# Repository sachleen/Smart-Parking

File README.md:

Smart Parking ([GitHub][1])
=============

A system to monitor parking space availability and help drivers quickly find a nearby place to park.

[California State University, Sacramento][2]

Computer Engineering Senior Design Project

Team #4

 - Sachleen Sandhu
 - Caleb Fountain
 - Phillip Booker

  [1]: https://github.com/sachleen/Smart-Parking
  [2]: http://csus.edu

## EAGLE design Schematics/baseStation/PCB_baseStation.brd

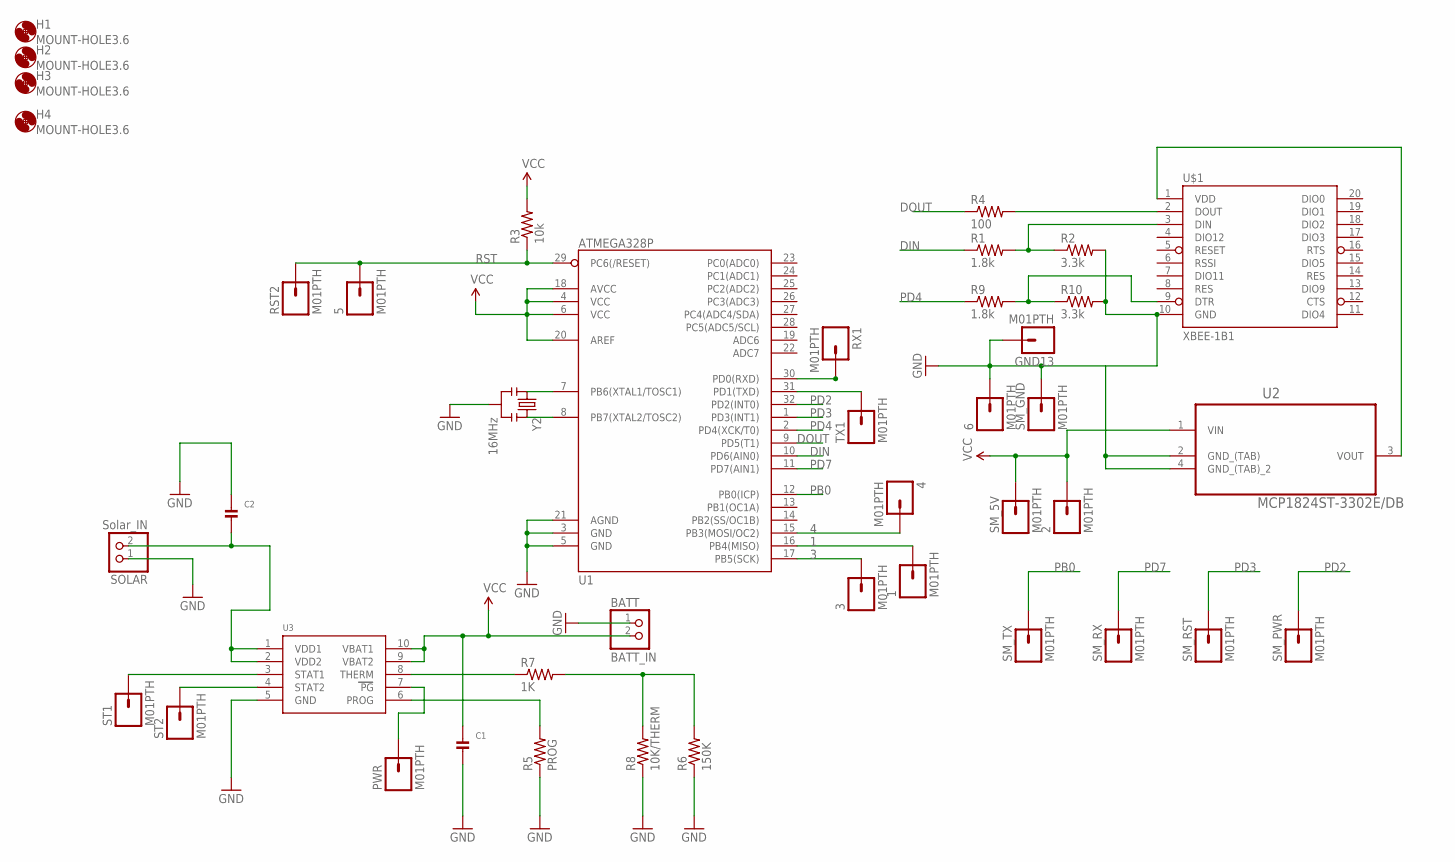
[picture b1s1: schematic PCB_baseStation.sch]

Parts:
1, 2, 3, 4, 5, 6: M01PTH; 1X01
BATT: BATT_IN; JSTPH2
C1, C2: CAP_CERAMIC0805; 0805
GND13: M01PTH; 1X01
H1, H2, H3, H4: MOUNT-HOLE3.6; 3,6
PWR: M01PTH; 1X01
R1, R9: 1.8k; 0603-RES
R2, R10: 3.3k; 0603-RES
R3: 10k; 1206
R4: 100; 0603-RES
R5: PROG; 0805-THM
R6: 150K; M0805
R7: 1K; M0805
R8: 10K/THERM; 0805-THM
RST2: M01PTH; 1X01
RX1: M01PTH; 1X01
SM_5V: M01PTH; 1X01
SM_GND: M01PTH; 1X01
SM_PWR: M01PTH; 1X01
SM_RST: M01PTH; 1X01
SM_RX: M01PTH; 1X01
SM_TX: M01PTH; 1X01
SOLAR: Solar_IN; JSTPH2
ST1, ST2: M01PTH; 1X01
TX1: M01PTH; 1X01
U1: ATMEGA328P; TQFP32-08
U2: MCP1824ST-3302E/DB; SOT230P700X180-4N
U3: MCP73833; MSOP10
U$1: XBEE-1B1; XBEE-1
Y2: 16MHz; RESONATOR-SMD

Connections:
1: 1.1, U1.16 (PB4(MISO))
3: 3.1, U1.17 (PB5(SCK))
4: 4.1, U1.15 (PB3(MOSI/OC2))
DIN: R1.1, U1.10 (PD6(AIN0))
DOUT: R4.1, U1.9 (PD5(T1))
GND: 6.1, BATT.1, C1.2, C2.1, GND13.1, R2.2, R5.1, R6.1, R8.1, R10.2, SM_GND.1, SOLAR.1, U1.3 (GND), U1.5 (GND), U1.21 (AGND), U2.2 (GND_(TAB)), U2.4 (GND_(TAB)_2), U3.5 (GND), U$1.10 (GND), Y2.2
unnamed: ST1.1, U3.3 (STAT1)
unnamed: ST2.1, U3.4 (STAT2)
unnamed: R1.2, R2.1, U$1.3 (DIN)
unnamed: R4.2, U$1.2 (DOUT)
unnamed: R9.2, R10.1, U$1.9 (DTR)
unnamed: U1.7 (PB6(XTAL1/TOSC1)), Y2.1
unnamed: U1.8 (PB7(XTAL2/TOSC2)), Y2.3
unnamed: C2.2, SOLAR.2, U3.1 (VDD1), U3.2 (VDD2)
unnamed: R5.2, U3.6 (PROG)
unnamed: PWR.1, U3.7 (PG)
unnamed: R6.2, R7.2, R8.2
unnamed: U2.3 (VOUT), U$1.1 (VDD)
unnamed: R7.1, U3.8 (THERM)
unnamed: TX1.1, U1.31 (PD1(TXD))
unnamed: RX1.1, U1.30 (PD0(RXD))
PB0: SM_TX.1, U1.12 (PB0(ICP))
PD2: SM_PWR.1, U1.32 (PD2(INT0))
PD3: SM_RST.1, U1.1 (PD3(INT1))
PD4: R9.1, U1.2 (PD4(XCK/T0))
PD7: SM_RX.1, U1.11 (PD7(AIN1))
RST: 5.1, R3.1, RST2.1, U1.29 (PC6(/RESET))
VCC: 2.1, BATT.2, C1.1, R3.2, SM_5V.1, U1.4 (VCC), U1.6 (VCC), U1.18 (AVCC), U1.20 (AREF), U2.1 (VIN), U3.9 (VBAT2), U3.10 (VBAT1)

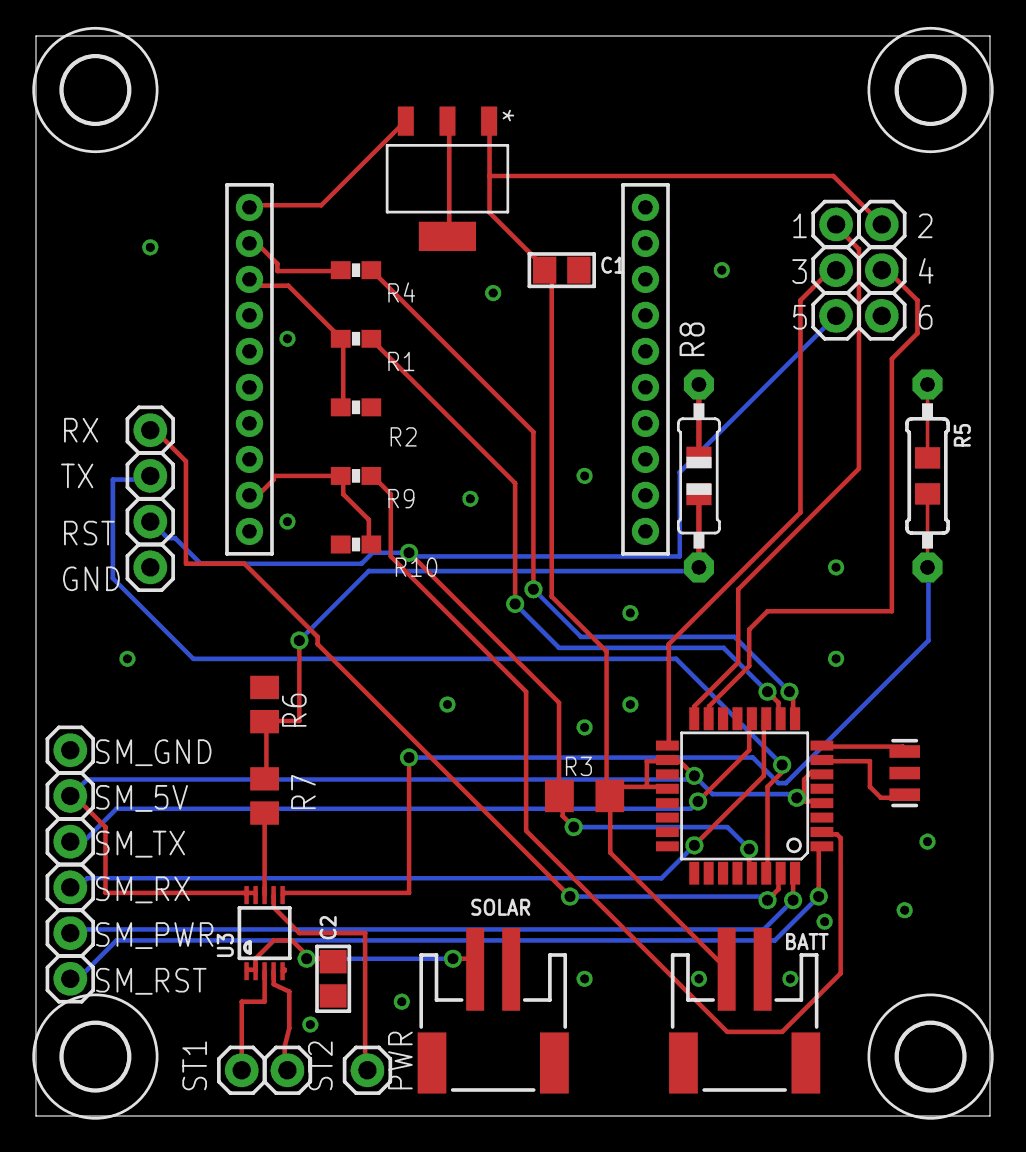
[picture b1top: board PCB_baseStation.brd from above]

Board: 2 copper layers, 53.0 x 60.0 mm, 42 parts (0 on the bottom side), 28 nets.

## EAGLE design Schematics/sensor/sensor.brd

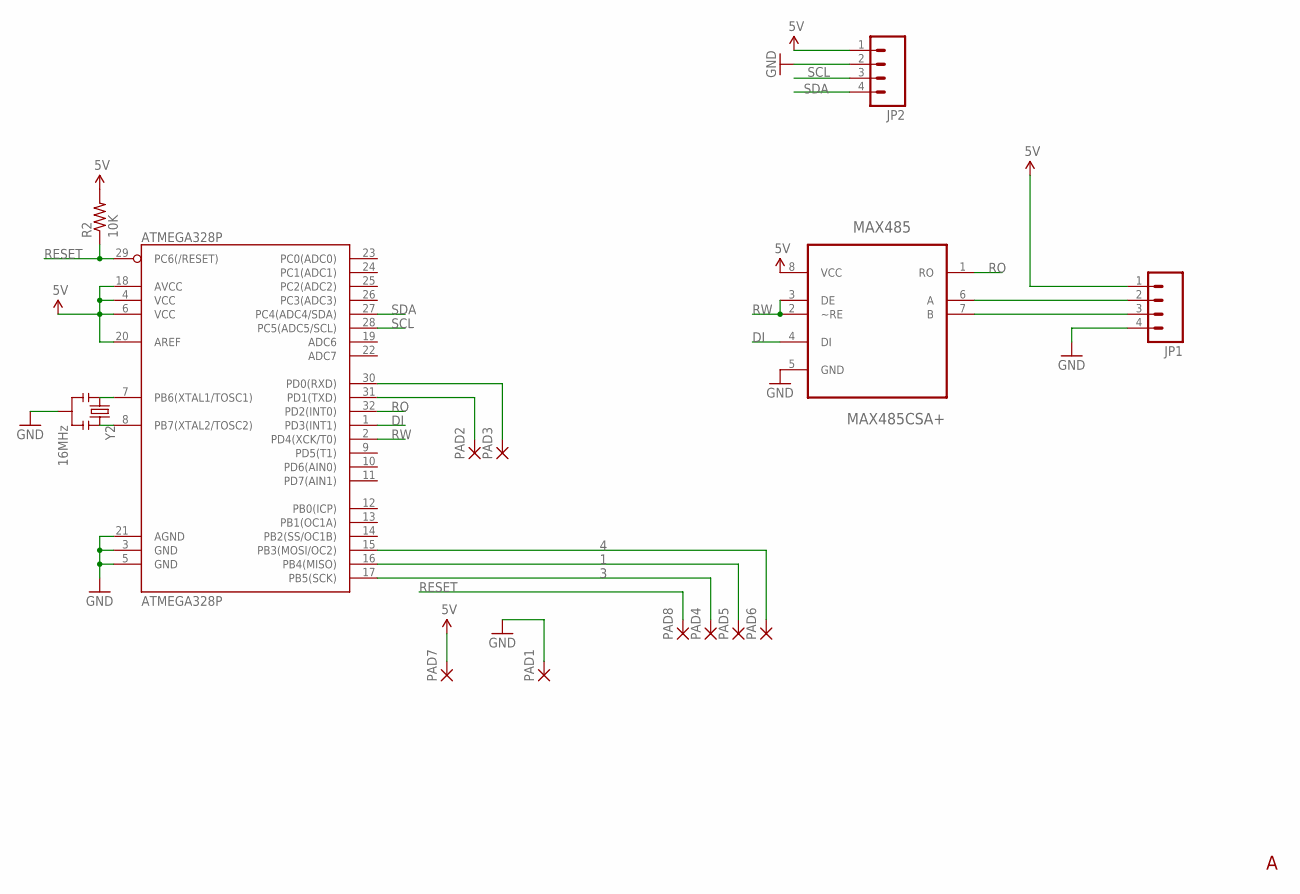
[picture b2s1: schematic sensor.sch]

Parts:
ATMEGA328P: ATMEGA328P; TQFP32-08
JP1, JP2: M04PTH; 1X04
MAX485: MAX485CSA+; SOIC127P600X175-8N
PAD1, PAD2, PAD3, PAD4, PAD5, PAD6, PAD7, PAD8: 1,6/0,9
R2: 10K; 0603-RES
Y2: 16MHz; RESONATOR-SMD

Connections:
1: ATMEGA328P.16 (PB4(MISO)), PAD5.1
3: ATMEGA328P.17 (PB5(SCK)), PAD4.1
4: ATMEGA328P.15 (PB3(MOSI/OC2)), PAD6.1
5V: ATMEGA328P.4 (VCC), ATMEGA328P.6 (VCC), ATMEGA328P.18 (AVCC), ATMEGA328P.20 (AREF), JP1.1, JP2.1, MAX485.8 (VCC), PAD7.1, R2.2
DI: ATMEGA328P.1 (PD3(INT1)), MAX485.4 (DI)
GND: ATMEGA328P.3 (GND), ATMEGA328P.5 (GND), ATMEGA328P.21 (AGND), JP1.4, JP2.2, MAX485.5 (GND), PAD1.1, Y2.2
unnamed: ATMEGA328P.7 (PB6(XTAL1/TOSC1)), Y2.1
unnamed: ATMEGA328P.8 (PB7(XTAL2/TOSC2)), Y2.3
unnamed: ATMEGA328P.30 (PD0(RXD)), PAD3.1
unnamed: JP1.2, MAX485.6 (A)
unnamed: JP1.3, MAX485.7 (B)
unnamed: ATMEGA328P.31 (PD1(TXD)), PAD2.1
RESET: ATMEGA328P.29 (PC6(/RESET)), PAD8.1, R2.1
RO: ATMEGA328P.32 (PD2(INT0)), MAX485.1 (RO)
RW: ATMEGA328P.2 (PD4(XCK/T0)), MAX485.2 (~RE), MAX485.3 (DE)
SCL: ATMEGA328P.28 (PC5(ADC5/SCL)), JP2.3
SDA: ATMEGA328P.27 (PC4(ADC4/SDA)), JP2.4

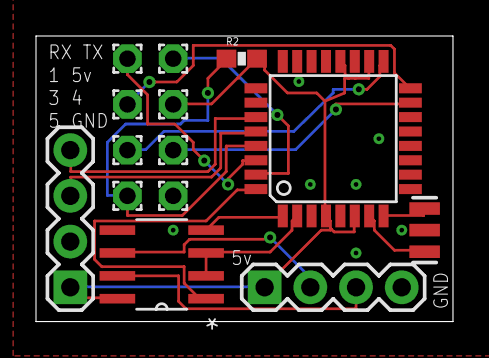
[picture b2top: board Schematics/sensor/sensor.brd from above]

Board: 2 copper layers, 23.2 x 15.9 mm, 14 parts (0 on the bottom side), 17 nets.

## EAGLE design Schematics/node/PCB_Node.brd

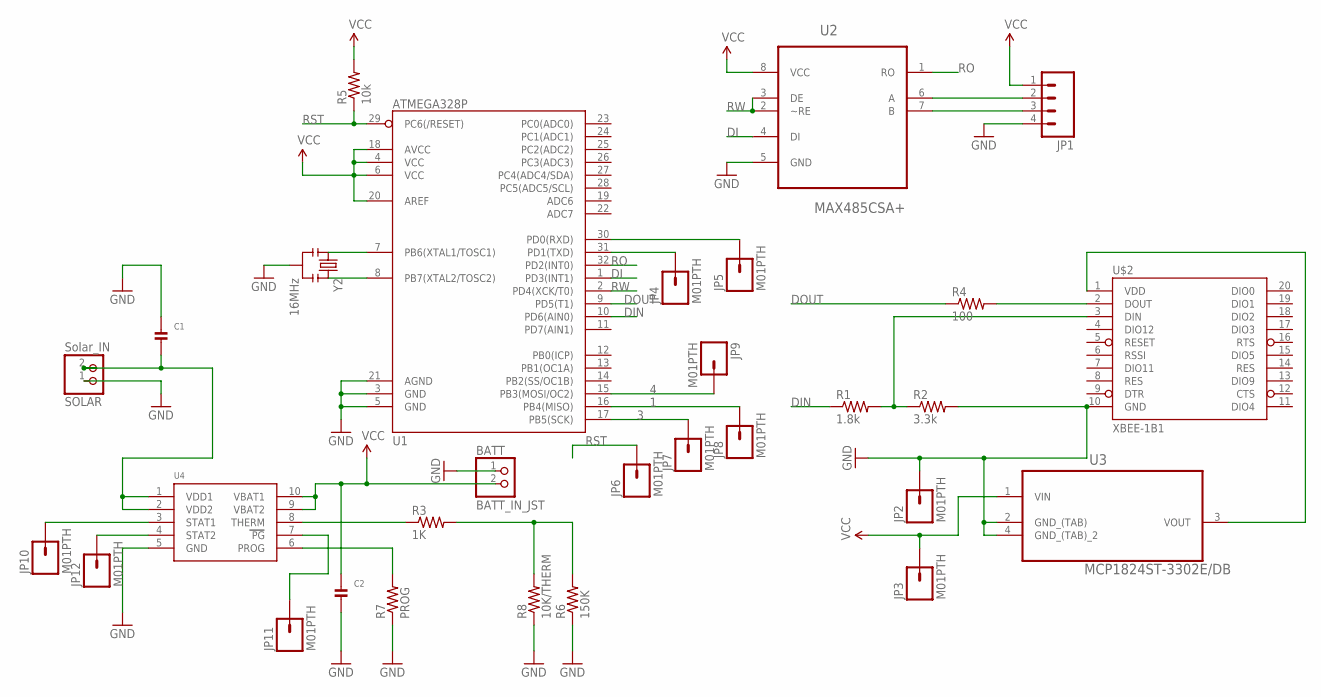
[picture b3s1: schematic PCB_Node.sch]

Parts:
BATT: BATT_IN_JST; JSTPH2
C1, C2: CAP_CERAMIC0805; 0805
JP1: M04PTH; 1X04
JP2, JP3, JP4, JP5, JP6, JP7, JP8, JP9, JP10, JP11, JP12: M01PTH; 1X01
R1: 1.8k; 0603-RES
R2: 3.3k; 0603-RES
R3: 1K; R0805
R4: 100; 0603-RES
R5: 10k; 0603-RES
R6: 150K; R0805
R7: PROG; 0805-THM
R8: 10K/THERM; 0805-THM
SOLAR: Solar_IN; JSTPH2
U1: ATMEGA328P; TQFP32-08
U2: MAX485CSA+; SOIC127P600X175-8N
U3: MCP1824ST-3302E/DB; SOT230P700X180-4N
U4: MCP73833; MSOP10
U$2: XBEE-1B1; XBEE-1
Y2: 16MHz; RESONATOR-SMD

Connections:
1: JP8.1, U1.16 (PB4(MISO))
3: JP7.1, U1.17 (PB5(SCK))
4: JP9.1, U1.15 (PB3(MOSI/OC2))
DI: U1.1 (PD3(INT1)), U2.4 (DI)
DIN: R1.1, U1.10 (PD6(AIN0))
DOUT: R4.1, U1.9 (PD5(T1))
GND: BATT.1, C1.1, C2.2, JP1.4, JP2.1, R2.2, R6.1, R7.1, R8.1, SOLAR.1, U1.3 (GND), U1.5 (GND), U1.21 (AGND), U2.5 (GND), U3.2 (GND_(TAB)), U3.4 (GND_(TAB)_2), U4.5 (GND), U$2.10 (GND), Y2.2
unnamed: R4.2, U$2.2 (DOUT)
unnamed: R1.2, R2.1, U$2.3 (DIN)
unnamed: R7.2, U4.6 (PROG)
unnamed: U3.3 (VOUT), U$2.1 (VDD)
unnamed: R3.1, U4.8 (THERM)
unnamed: R3.2, R6.2, R8.2
unnamed: C1.2, SOLAR.2, U4.1 (VDD1), U4.2 (VDD2)
unnamed: JP10.1, U4.3 (STAT1)
unnamed: JP12.1, U4.4 (STAT2)
unnamed: JP11.1, U4.7 (PG)
unnamed: U1.8 (PB7(XTAL2/TOSC2)), Y2.3
unnamed: U1.7 (PB6(XTAL1/TOSC1)), Y2.1
unnamed: JP4.1, U1.31 (PD1(TXD))
unnamed: JP5.1, U1.30 (PD0(RXD))
unnamed: JP1.2, U2.6 (A)
unnamed: JP1.3, U2.7 (B)
RO: U1.32 (PD2(INT0)), U2.1 (RO)
RST: JP6.1, R5.1, U1.29 (PC6(/RESET))
RW: U1.2 (PD4(XCK/T0)), U2.2 (~RE), U2.3 (DE)
VCC: BATT.2, C2.1, JP1.1, JP3.1, R5.2, U1.4 (VCC), U1.6 (VCC), U1.18 (AVCC), U1.20 (AREF), U2.8 (VCC), U3.1 (VIN), U4.9 (VBAT2), U4.10 (VBAT1)

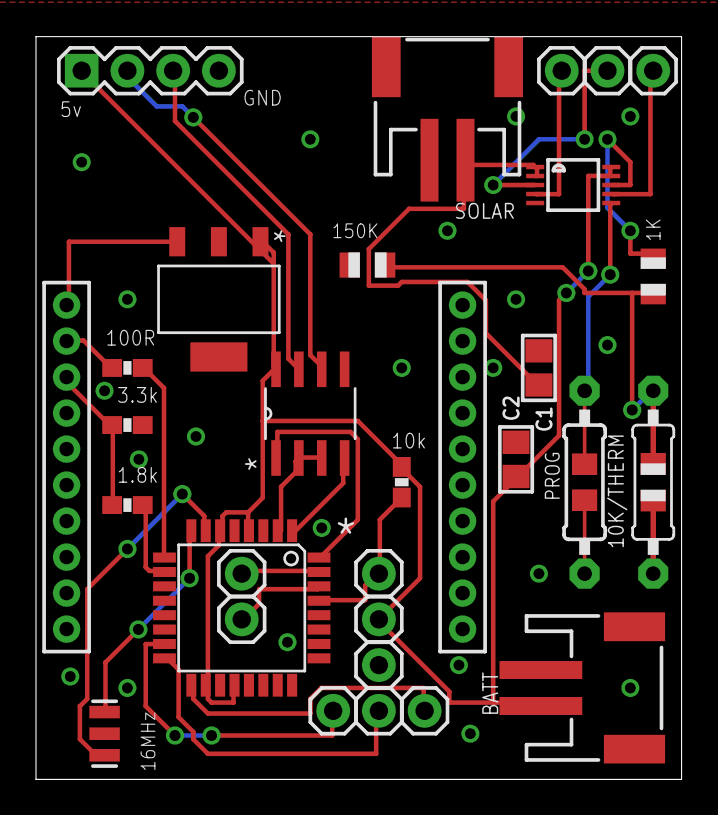
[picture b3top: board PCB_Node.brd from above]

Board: 2 copper layers, 35.9 x 41.3 mm, 30 parts (0 on the bottom side), 27 nets.

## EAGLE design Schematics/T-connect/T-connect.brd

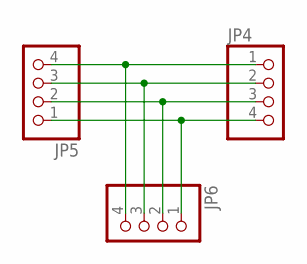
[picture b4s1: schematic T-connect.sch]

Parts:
JP4, JP5, JP6: PINHD-1X4/90; 1X04/90

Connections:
unnamed: JP4.1, JP5.4, JP6.4
unnamed: JP4.2, JP5.3, JP6.3
unnamed: JP4.3, JP5.2, JP6.2
unnamed: JP4.4, JP5.1, JP6.1

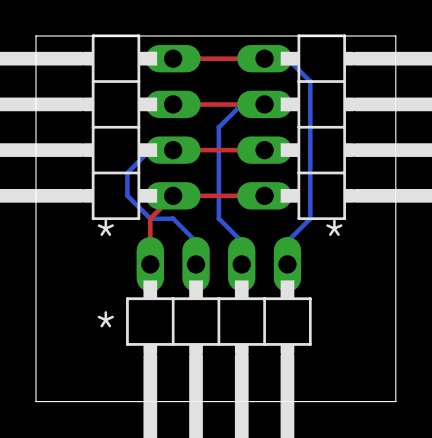
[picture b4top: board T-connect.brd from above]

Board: 2 copper layers, 20.0 x 20.3 mm, 3 parts (0 on the bottom side), 4 nets.

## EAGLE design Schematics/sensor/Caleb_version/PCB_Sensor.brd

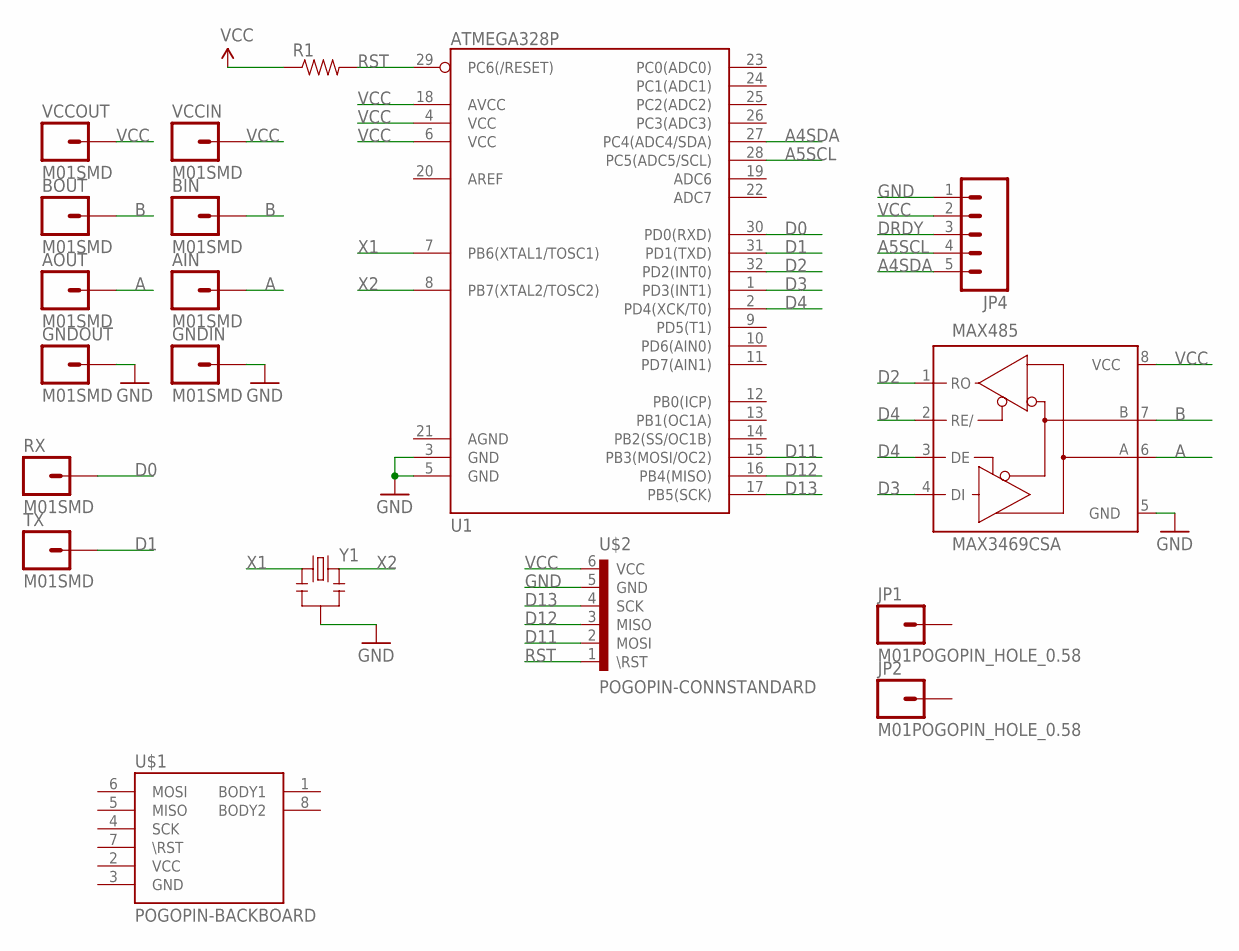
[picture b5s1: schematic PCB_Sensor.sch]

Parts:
AIN: M01SMD; LUXEON-PAD
AOUT: M01SMD; LUXEON-PAD
BIN: M01SMD; LUXEON-PAD
BOUT: M01SMD; LUXEON-PAD
GNDIN: M01SMD; LUXEON-PAD
GNDOUT: M01SMD; LUXEON-PAD
JP1, JP2: M01POGOPIN_HOLE_0.58; 1X01_POGOPIN_HOLE_0.58
JP4: M05PTH; 1X05
MAX485: MAX3469CSA; SO08
R1: RESISTOR1206; 1206
RX: M01SMD; LUXEON-PAD
TX: M01SMD; LUXEON-PAD
U1: ATMEGA328P; TQFP32-08
U$1: POGOPIN-BACKBOARD; POGOPROG-BACKMOUNT
U$2: POGOPIN-CONNSTANDARD; POGOPROG-CONN
VCCIN: M01SMD; LUXEON-PAD
VCCOUT: M01SMD; LUXEON-PAD
Y1: RESONATORPTH; RESONATOR-PTH

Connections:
A: AIN.P$1, MAX485.6 (A)
A4SDA: JP4.5, U1.27 (PC4(ADC4/SDA))
A5SCL: JP4.4, U1.28 (PC5(ADC5/SCL))
B: BIN.P$1, MAX485.7 (B)
D0: U1.30 (PD0(RXD))
D1: U1.31 (PD1(TXD))
D2: MAX485.1 (RO), U1.32 (PD2(INT0))
D3: MAX485.4 (DI), U1.1 (PD3(INT1))
D4: MAX485.2 (RE/), MAX485.3 (DE), U1.2 (PD4(XCK/T0))
D11: U1.15 (PB3(MOSI/OC2)), U$2.2 (MOSI)
D12: U1.16 (PB4(MISO)), U$2.3 (MISO)
D13: U1.17 (PB5(SCK)), U$2.4 (SCK)
DRDY: JP4.3
GND: GNDIN.P$1, JP4.1, MAX485.5 (GND), U1.3 (GND), U1.5 (GND), U$2.5 (GND), Y1.2
RST: R1.2, U1.29 (PC6(/RESET)), U$2.1 (\RST)
VCC: JP4.2, MAX485.8 (VCC), R1.1, U1.4 (VCC), U1.6 (VCC), U1.18 (AVCC), U$2.6 (VCC), VCCIN.P$1, VCCOUT.P$1
X1: U1.7 (PB6(XTAL1/TOSC1)), Y1.1
X2: U1.8 (PB7(XTAL2/TOSC2)), Y1.3

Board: 2 copper layers, 19 parts (0 on the bottom side), 15 nets, no tracks yet.

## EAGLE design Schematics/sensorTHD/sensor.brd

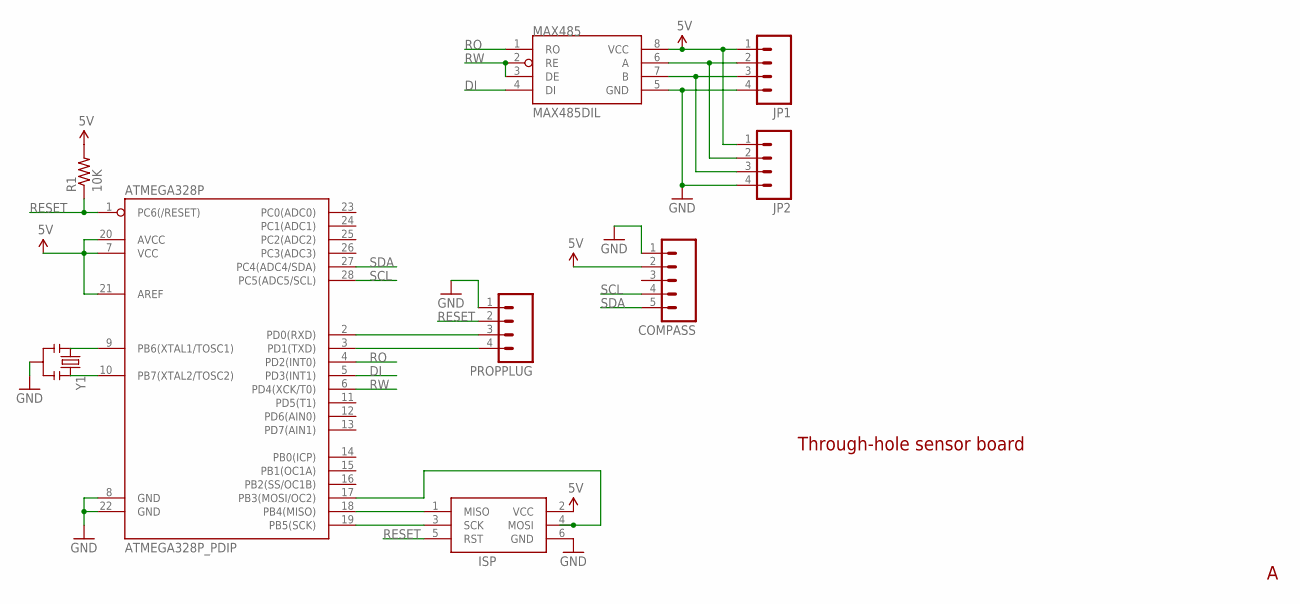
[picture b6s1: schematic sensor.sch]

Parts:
ATMEGA328P: ATMEGA328P_PDIP; DIL28-3
COMPASS: M05PTH; 1X05
ISP: AVRISP-6; AVRISP
JP1, JP2: M04PTH; 1X04
MAX485: MAX485DIL; DIL08
PROPPLUG: M04PTH; 1X04
R1: 10K; AXIAL-0.4
Y1: RESONATORPTH; RESONATOR-PTH

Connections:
5V: ATMEGA328P.7 (VCC), ATMEGA328P.20 (AVCC), ATMEGA328P.21 (AREF), COMPASS.2, ISP.2 (VCC), JP1.1, JP2.1, MAX485.8 (VCC), R1.P$2 (2)
DI: ATMEGA328P.5 (PD3(INT1)), MAX485.4 (DI)
GND: ATMEGA328P.8 (GND), ATMEGA328P.22 (GND), COMPASS.1, ISP.6 (GND), JP1.4, JP2.4, MAX485.5 (GND), PROPPLUG.1, Y1.2
unnamed: ATMEGA328P.10 (PB7(XTAL2/TOSC2)), Y1.3
unnamed: ATMEGA328P.9 (PB6(XTAL1/TOSC1)), Y1.1
unnamed: ATMEGA328P.18 (PB4(MISO)), ISP.1 (MISO)
unnamed: ATMEGA328P.19 (PB5(SCK)), ISP.3 (SCK)
unnamed: ATMEGA328P.17 (PB3(MOSI/OC2)), ISP.4 (MOSI)
unnamed: ATMEGA328P.2 (PD0(RXD)), PROPPLUG.3
unnamed: ATMEGA328P.3 (PD1(TXD)), PROPPLUG.4
unnamed: JP1.3, JP2.3, MAX485.7 (B)
unnamed: JP1.2, JP2.2, MAX485.6 (A)
RESET: ATMEGA328P.1 (PC6(/RESET)), ISP.5 (RST), PROPPLUG.2, R1.P$1 (1)
RO: ATMEGA328P.4 (PD2(INT0)), MAX485.1 (RO)
RW: ATMEGA328P.6 (PD4(XCK/T0)), MAX485.2 (RE), MAX485.3 (DE)
SCL: ATMEGA328P.28 (PC5(ADC5/SCL)), COMPASS.4
SDA: ATMEGA328P.27 (PC4(ADC4/SDA)), COMPASS.5

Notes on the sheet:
Through-hole sensor board

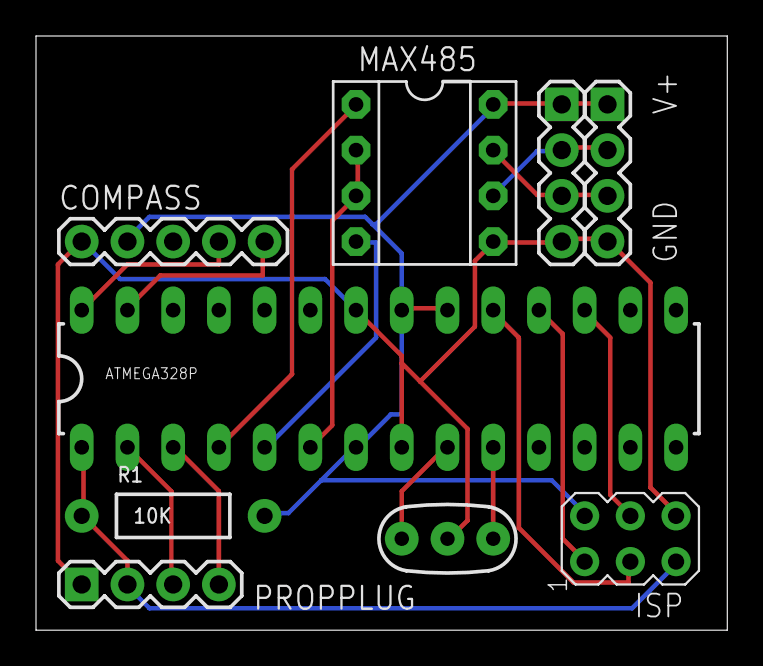
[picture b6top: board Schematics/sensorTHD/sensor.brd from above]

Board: 2 copper layers, 38.4 x 33.0 mm, 9 parts (0 on the bottom side), 17 nets.

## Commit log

2014-01-02 no message
2014-01-02 test
2014-01-02 Creating folder structure
2014-01-02 Added team info
2014-01-03 Initial commit.
2014-01-05 Worked on adding and editing Node markers on map. Still need to add delete feature.
2014-01-05 Added delete function Cleaned up (removed) console.log messages
2014-01-05 Front end functionality complete. Add/Delete nodes works.
2014-01-06 Added database functionality. Create, Edit, Delete work.
2014-01-06 App parses responses from server and displays user-friendly message now.
2014-01-06 Fancy message boxes!
2014-01-06 Created simple client app
2014-01-06 Opens device's Maps app when clicking on marker
2014-01-06 Clean up.
2014-01-07 Client updates automatically as map is panned. Loads all markers within a fixed distance of the map center.
2014-01-07 Added current location marker
2014-01-07 Added production/development modes
2014-01-07 Handled case where zooming in/out was not triggering new data load
2014-01-07 Made dev/prod mode switching easier.
2014-01-07 Put distance calculating SQL query into a function. Removed mysql passwords from index.php. oops
2014-01-07 Added htaccess to deny access to vendor directory
2014-01-10 Added a license
2014-02-02 Sensor schematics and board layouts
2014-02-02 Changed headers for 485 bus and added more labels.
2014-02-08 Made sensor PCB smaller. Removed through hole circuit.
2014-02-09 Admin app only loads nodes within 1mi radius of map center now.
2014-02-09 Top/bottom ground planes weren't connected. Added via to connect them.
2014-02-11 Testing commit to README.md
2014-02-11 Revert "Testing commit to README.md"
    This reverts commit b2356239c0976946008ed139fd2cdaf01c163b69.
2014-02-14 Added simple API key authentication to update/delete methods.
2014-02-14 changed = to == in if statement.
2014-02-14 Updated db schema to for new api keys table
2014-02-17 RX and TX for PROPPLUG weren't connected. they are now.
2014-02-21 added config files for client/server apps
2014-02-22 * Updated api key privileges - combined create_or_update with delete. * convert node ID to upper case before storing it in database.
2014-02-22 Added history logging functionality.
2014-02-22 BASE_URL should contain trailing slash.
2014-02-22 Fixed typo
2014-02-23 Removed unused keys from response.
2014-02-23 Code cleanup
2014-02-24 Added ignore entry for eagle project file.
2014-03-01 Added function to get node info.
2014-03-02 Connector changed
    I changed connectors to the following
    Device: M01SMD (M01)
    Package: LUXEON-PAD
    Library: SparkFun-Connectors
2014-03-02 Revision by Caleb
    Changed programming connectors to be on the surface as pads only for
    programming with another board.
    Rearranged the board to minimize the size as much as possible.
    Dimensions are .95 x .65
2014-03-02 PCB Node
    Created schematic and board layout for Node PCB
2014-03-02 New test script. Initial commit.
2014-03-02 better eagle ignore rules.
2014-03-03 added more test cases
2014-03-15 Added my current code for Base and Node
2014-03-15 Initial commit for analytics site
2014-03-15 re-added /nodes/all function
2014-03-17 Added auto run script for demo of client app
2014-03-17 Shortened refresh timeout to 2 seconds (from 10s) and added auto refresh functionality.
2014-03-17 renamed centerChanged function to more generic loadNodesAtCurrentPosition
2014-03-17 Set timeout to 5s. Map only updates markers when there's a change. Added bounce animation on change.
2014-03-17 changed refresh rate.
2014-03-17 cleaned up marker animation code
2014-03-17 cleaned up code
2014-03-17 marker indicator count updates after animation to make it easier to see the change.
2014-03-17 added nodes list for some nodes on the production site.
2014-03-20 Cleaned up sensor code, split up main code from RS485 code. Added debug functions instead of Searial.println
2014-03-20 Updated Base and Node codes
2014-03-21 Converted wired communication stuff to a class.
2014-03-21 fixed typo in debug_init function.
2014-03-21 Changed all Serial prints to DEBUG. Integrated with WiredCommunication class.
2014-03-21 PCB updates
    changed sensor PCB to 3.0
    changed Node PCB to 2.0 and parts list to go with it (Sach, can you
    look over the schematic, board, and parts list that I have so far to
    make sure I have everything correct?)
    added Base Station PCB 0.5
2014-03-21 Corrected Node PCB issues found by Sachleen for version 2.0
2014-03-22 Added XBee communication class. Not integrated with Node code, yet.
2014-03-22 Moved RS485 initialization into WiredCommunication class.
2014-03-22 Remove old files
2014-03-22 Renamed new files.
2014-03-22 Include globals in WiredCommunications to allow for debug prints
2014-03-22 send message accepts an id and a message.
2014-03-23 changed message packet format to include sender and receiver.
2014-03-23 Using new communication functions.
2014-03-23 Accidentally uploaded Node as a C header file...
2014-03-23 add debug prints in xbee class. add xbee class to base
2014-03-23 have to include softwareserial in xbee comm... added globals.
2014-03-23 off by 1 error in message format
2014-03-23 Fixed ACK bug where sendMessage was always returning false because of \r\n at end of message.
2014-03-23 Trimmed response Strings
2014-03-23 Fixed Node Parsing
2014-03-23 Removed ACK checks
2014-03-23 Taking out acknowledges
2014-03-23 removed acknowledge stuff...
2014-03-23 Node Fixes
    Made fixes to Node PCB.
    - connected solar power to charging chip
    - made power to battery and atmega from charging chip only
    - rearranged board for these changes to work
2014-03-24 Completed SIM900 Communication class. Have methods to send commands and make HTTP Requests. Includes demo application.
2014-03-24 spacing
2014-03-25 Node fixes
    Corrected the c1 capacitor connected to solar power correctly
    moved part names to locations where they will be read because of vias
    blocking them
2014-03-25 Changed API keys in test scripts.
2014-03-29 Added SIM and Sleep functions
2014-03-29 fixed POST url
2014-03-29 Cleaned out unneeded functions
2014-03-29 Chenged api key
2014-03-29 removed call to freeram function
2014-03-29 Fixed bug where xbee and simcomm wouldn't work together. needed to switch between software serial devices.
2014-03-29 save ram store strings in flash
2014-03-29 Checked for NULL response from sim function
2014-03-29 trying to free memory
2014-03-30 Trying to cut Base code
2014-03-30 added free ram code
2014-03-30 Cut out N case
2014-03-30 Commented out debug messages
2014-03-30 minimal code for U command only. THIS WORKS.
2014-03-30 Hard coded URLs.
2014-03-30 Reverted to old code to test (left working one in comments)
2014-03-30 removed GET request functionality
2014-03-30 proper call to POST method
2014-03-30 Reverting to what worked after failed attempts...
2014-03-30 All code works with POST method only.
2014-03-31 PCB improvements
    Node_SP 2.0: moved some text to the back layer
    Sen_SP 4.0: improved the board for programming and changed the
    resonator from through hole to surface mount - then rearranged the
    items on the board to make it smaller
2014-03-31 Power optimizations in sensor.
2014-04-02 moved DEBUG_ENABLE line from globals.h to individual files
2014-04-02 Toggles power when it needs to send updates to the server
2014-04-02 compass sleep mode. saves about 0.1mA
2014-04-04 Base Station PCB 1.0
    Finished Base Station PCB design version 1.0
2014-04-06 Added Xbee and arduino sleep to Node
2014-04-06 Took out sleep library
2014-04-06 Base Station PCB improvements
    Base_SP 1.1
    moved prop plug and ISP closer in
    added two resistors to limit voltage from arduino to xbee pin 9(SLP)
2014-04-06 Base Station PCB Improvements
    Base_SP 1.2
    moved components around to group them better
    corrected xbee pin 9 to be connected from arduino PD4 to PD7
2014-04-07 Base Station PCB Improvements
    Base_SP 1.3
    fixed SIM900 pins that go to Arduino
    changed xbee pin that goes to Arduino
    created table of base Arduino pins and where they go to
2014-04-07 Revert 84d25af..6e9f095
    This rolls back to commit 84d25afdcd8c89c582355f2af172ebeae3c02958.
2014-04-07 Revert f17e3e6..3ebf404
    This rolls back to commit f17e3e6aa3351730fd70c4ce41f61063c92e8cc4.
2014-04-07 Revert 6e9f095..8a23197
    This rolls back to commit 6e9f095d9700ac4f46dd20743e80d1823ffcaa8e.
2014-04-08 Revert f17e3e6..f513072
    This rolls back to commit f17e3e6aa3351730fd70c4ce41f61063c92e8cc4.
2014-04-08 PCB Base Station Improvements
    Base_SP 1.4
    fixed issues that were occurring with code
    fixed SIM900 pins that go to Arduino
    changed xbee pin that goes to Arduino
    created table of base Arduino pins and where they go to
2014-04-11 Node and Sensor code that randomly assigns Sensor ID at Node startup
2014-04-14 Fixed Sensor Issues
2014-04-14 Fixed Network connect issue when sending updates
2014-04-16 Commented code and minor code clean-up
2014-04-21 Updated team members
2014-04-21 Base Station PCB Improvements
    Base_SP 1.5
    - Fix: connected Regulator for XBee to GND
2014-04-21 Code used for deployable prototype day
2014-04-21 Base Station PCB update
    Updated the version of the board that is printed on the back from 1.4
    to 1.5
2014-04-28 added comments
2014-05-06 added github link

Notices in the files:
parts and their libraries:
SparkFun-DigitalIC: Licensing: CC v3.0 Share-Alike You are welcome to use this library for commercial purposes.
microbuilder: This work is placed in the public domain, and may be freely used for commercial and non-commercial work with the following conditions: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
